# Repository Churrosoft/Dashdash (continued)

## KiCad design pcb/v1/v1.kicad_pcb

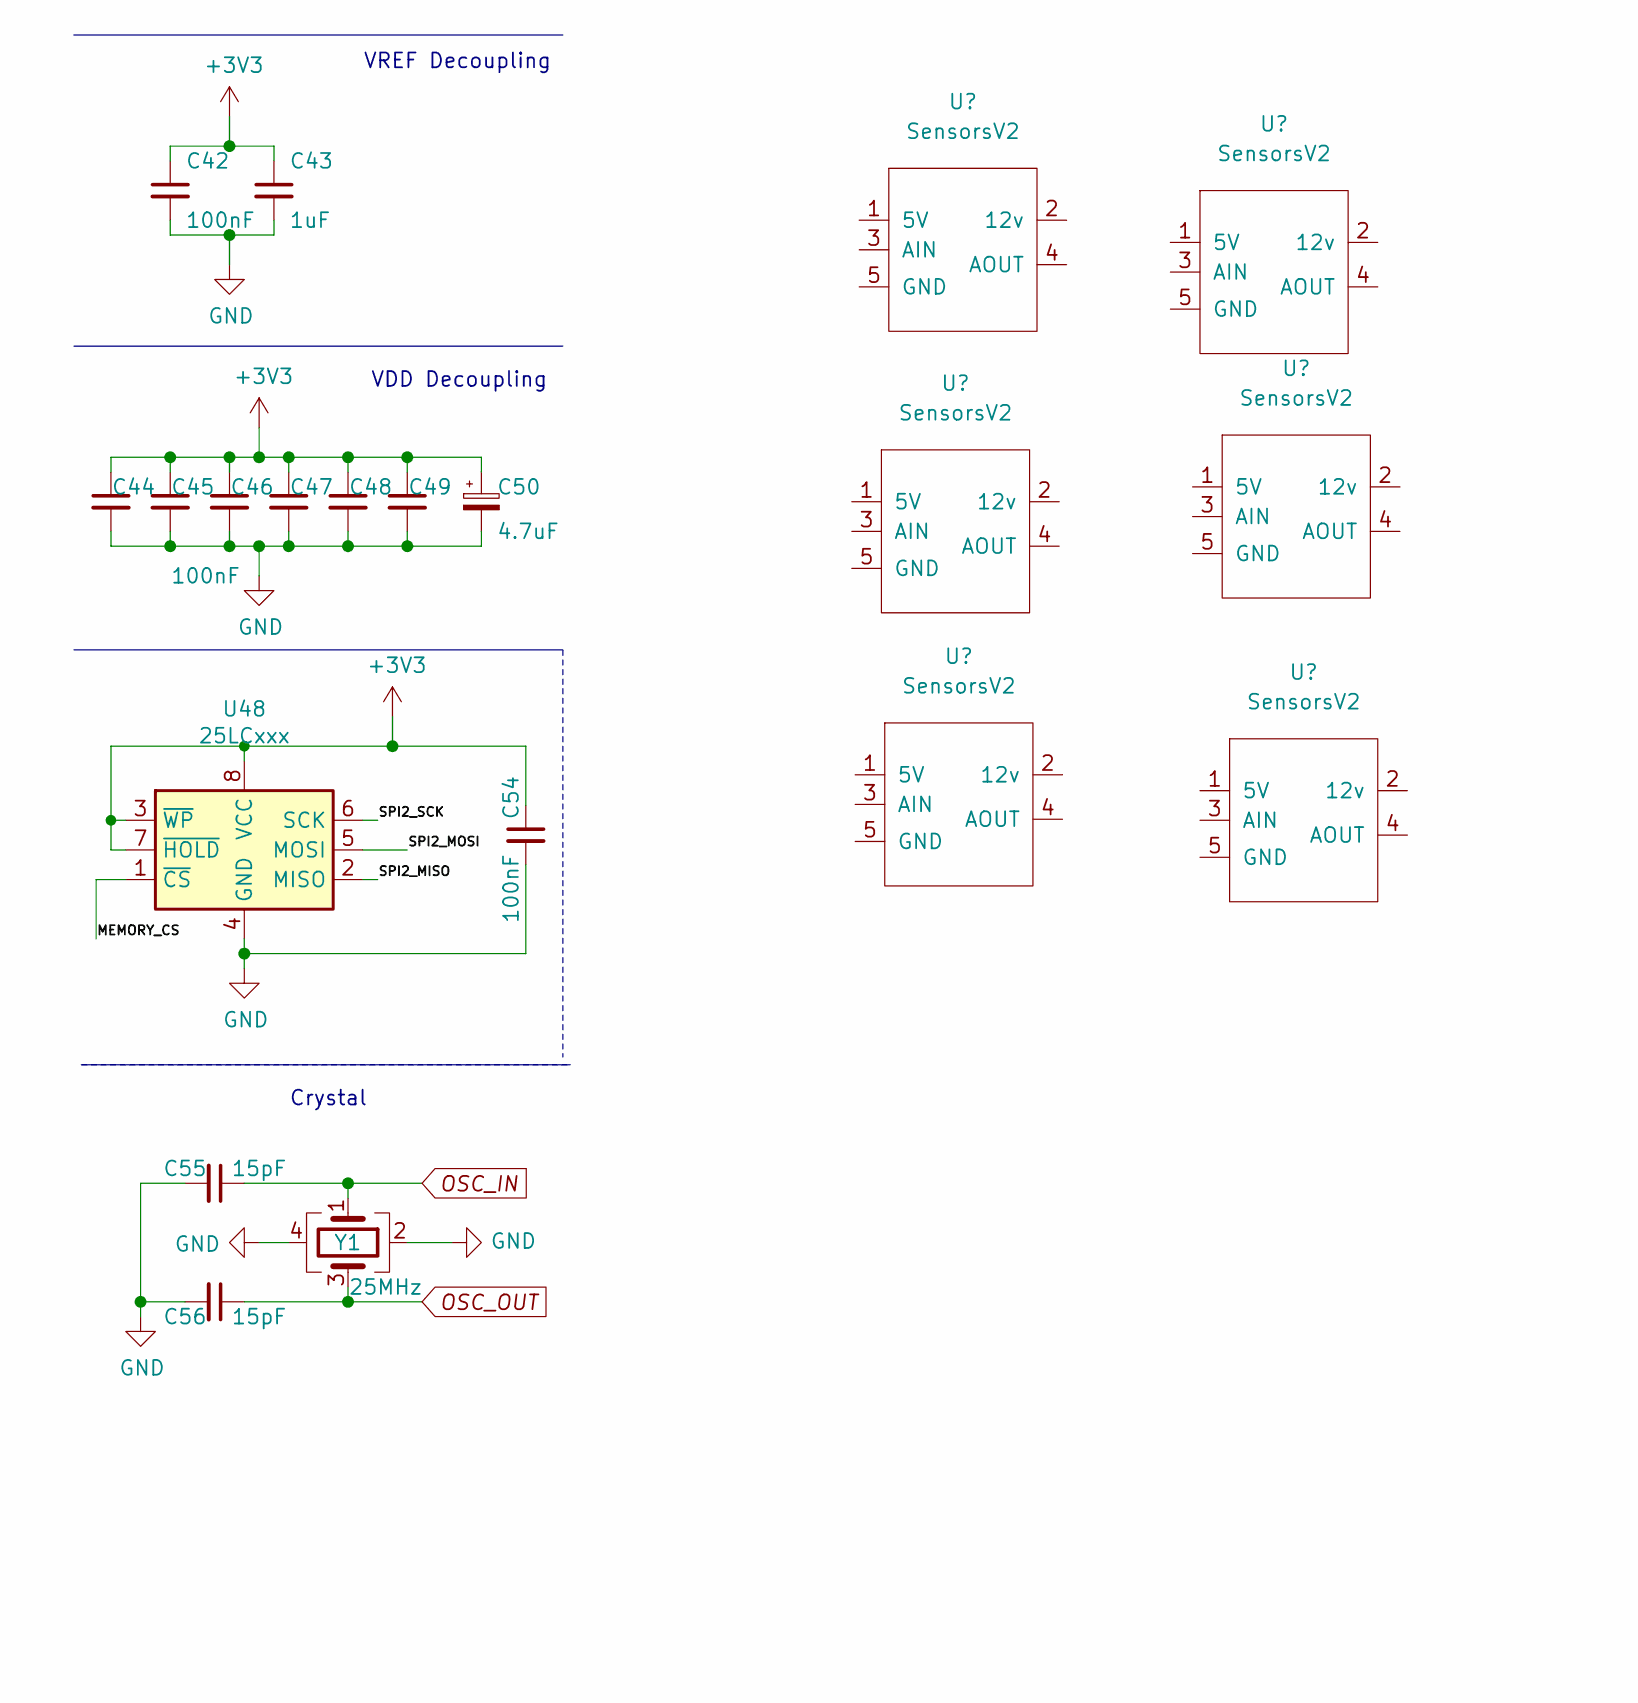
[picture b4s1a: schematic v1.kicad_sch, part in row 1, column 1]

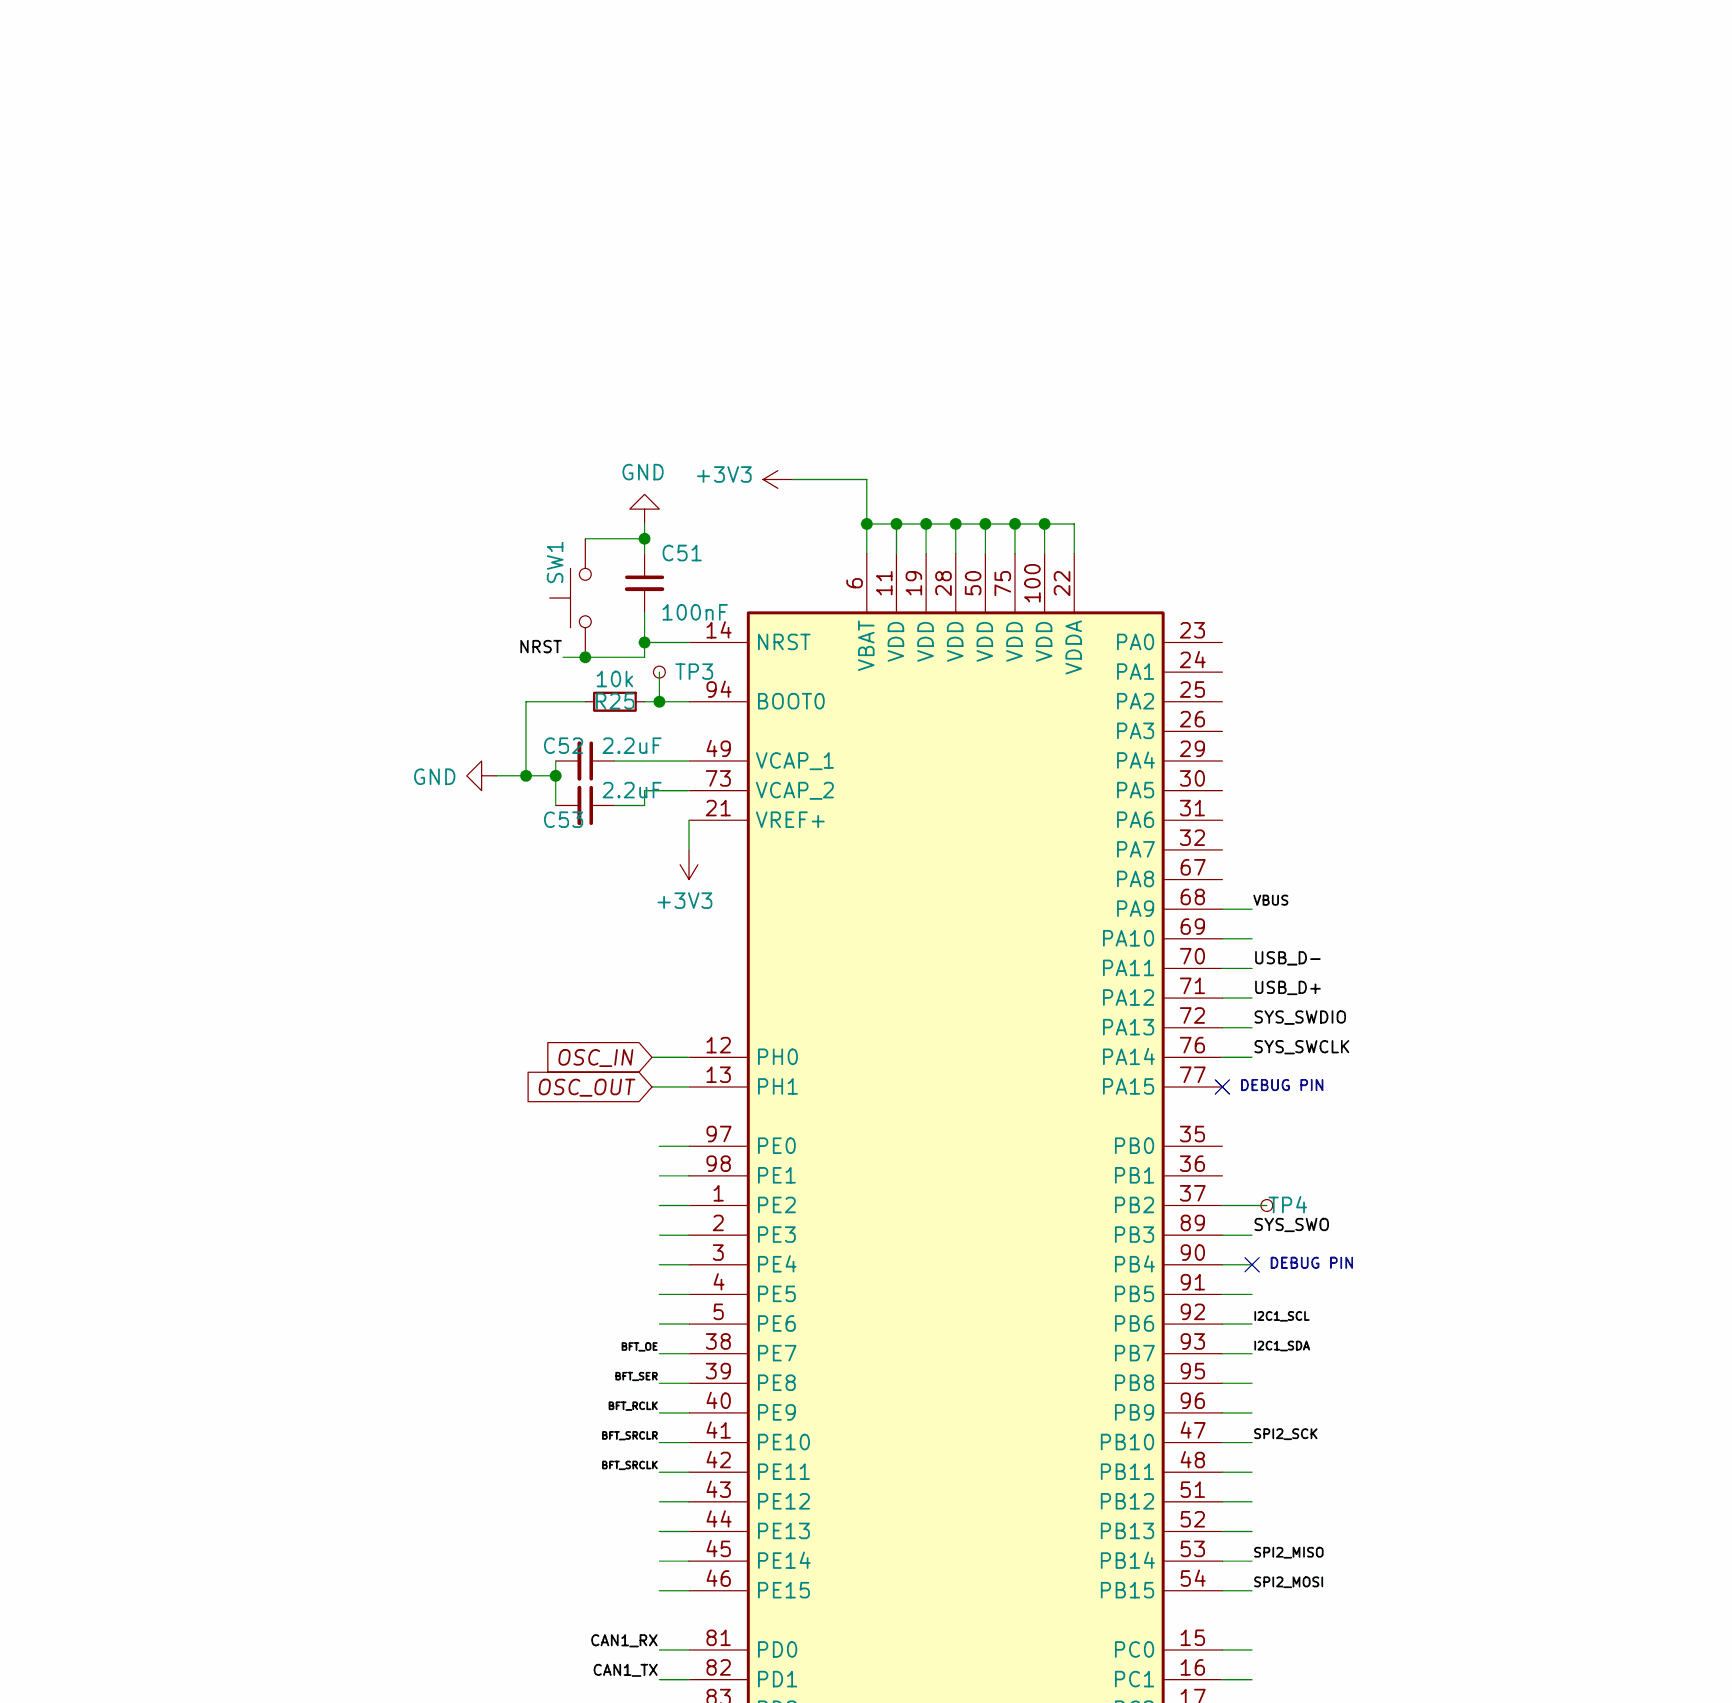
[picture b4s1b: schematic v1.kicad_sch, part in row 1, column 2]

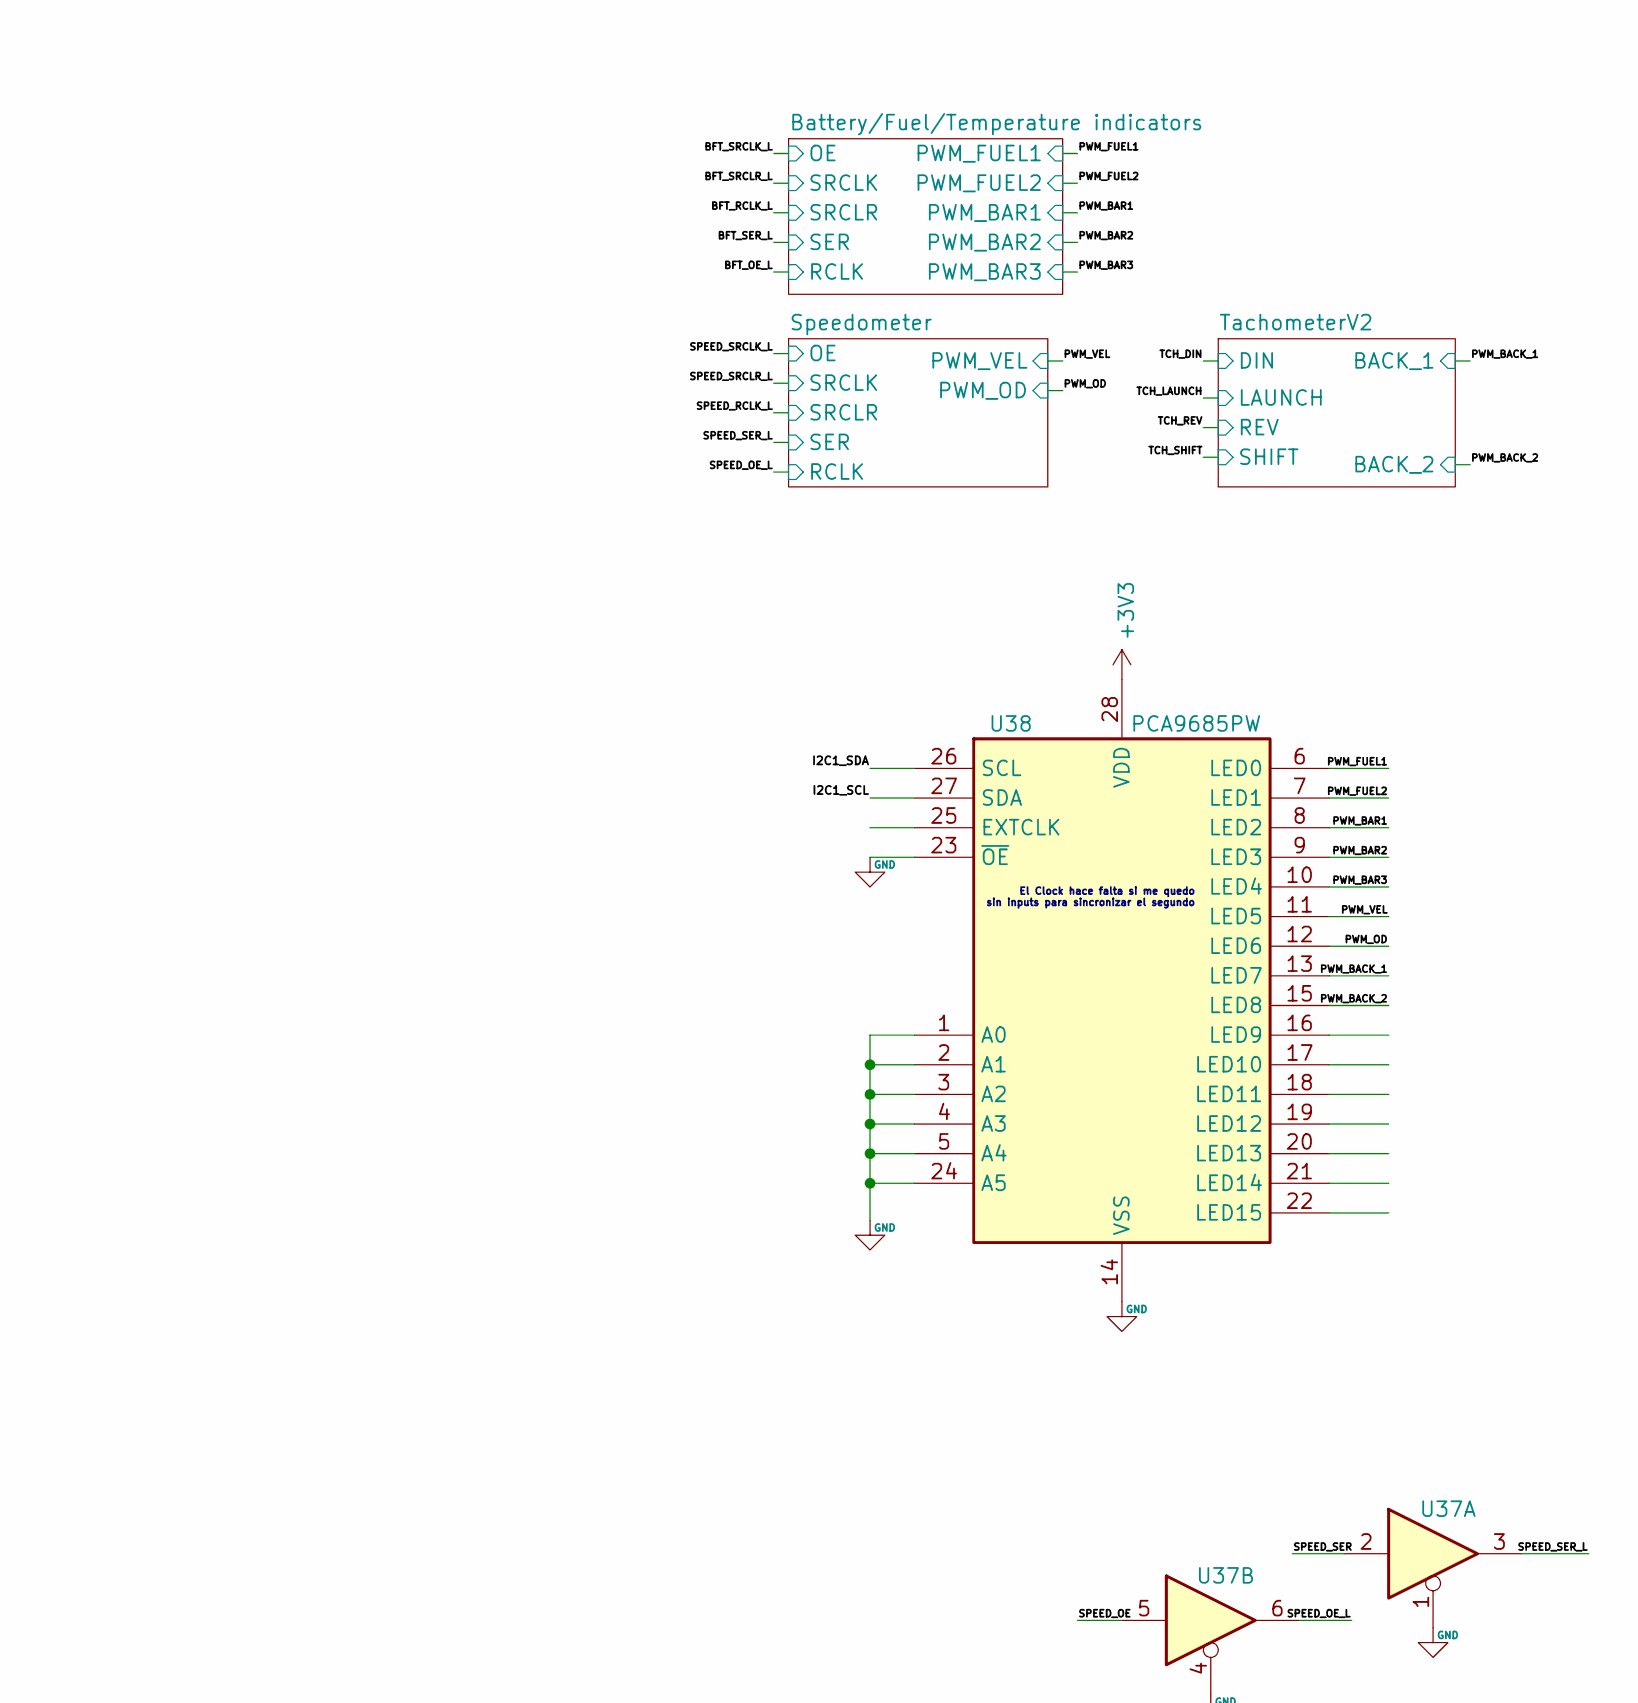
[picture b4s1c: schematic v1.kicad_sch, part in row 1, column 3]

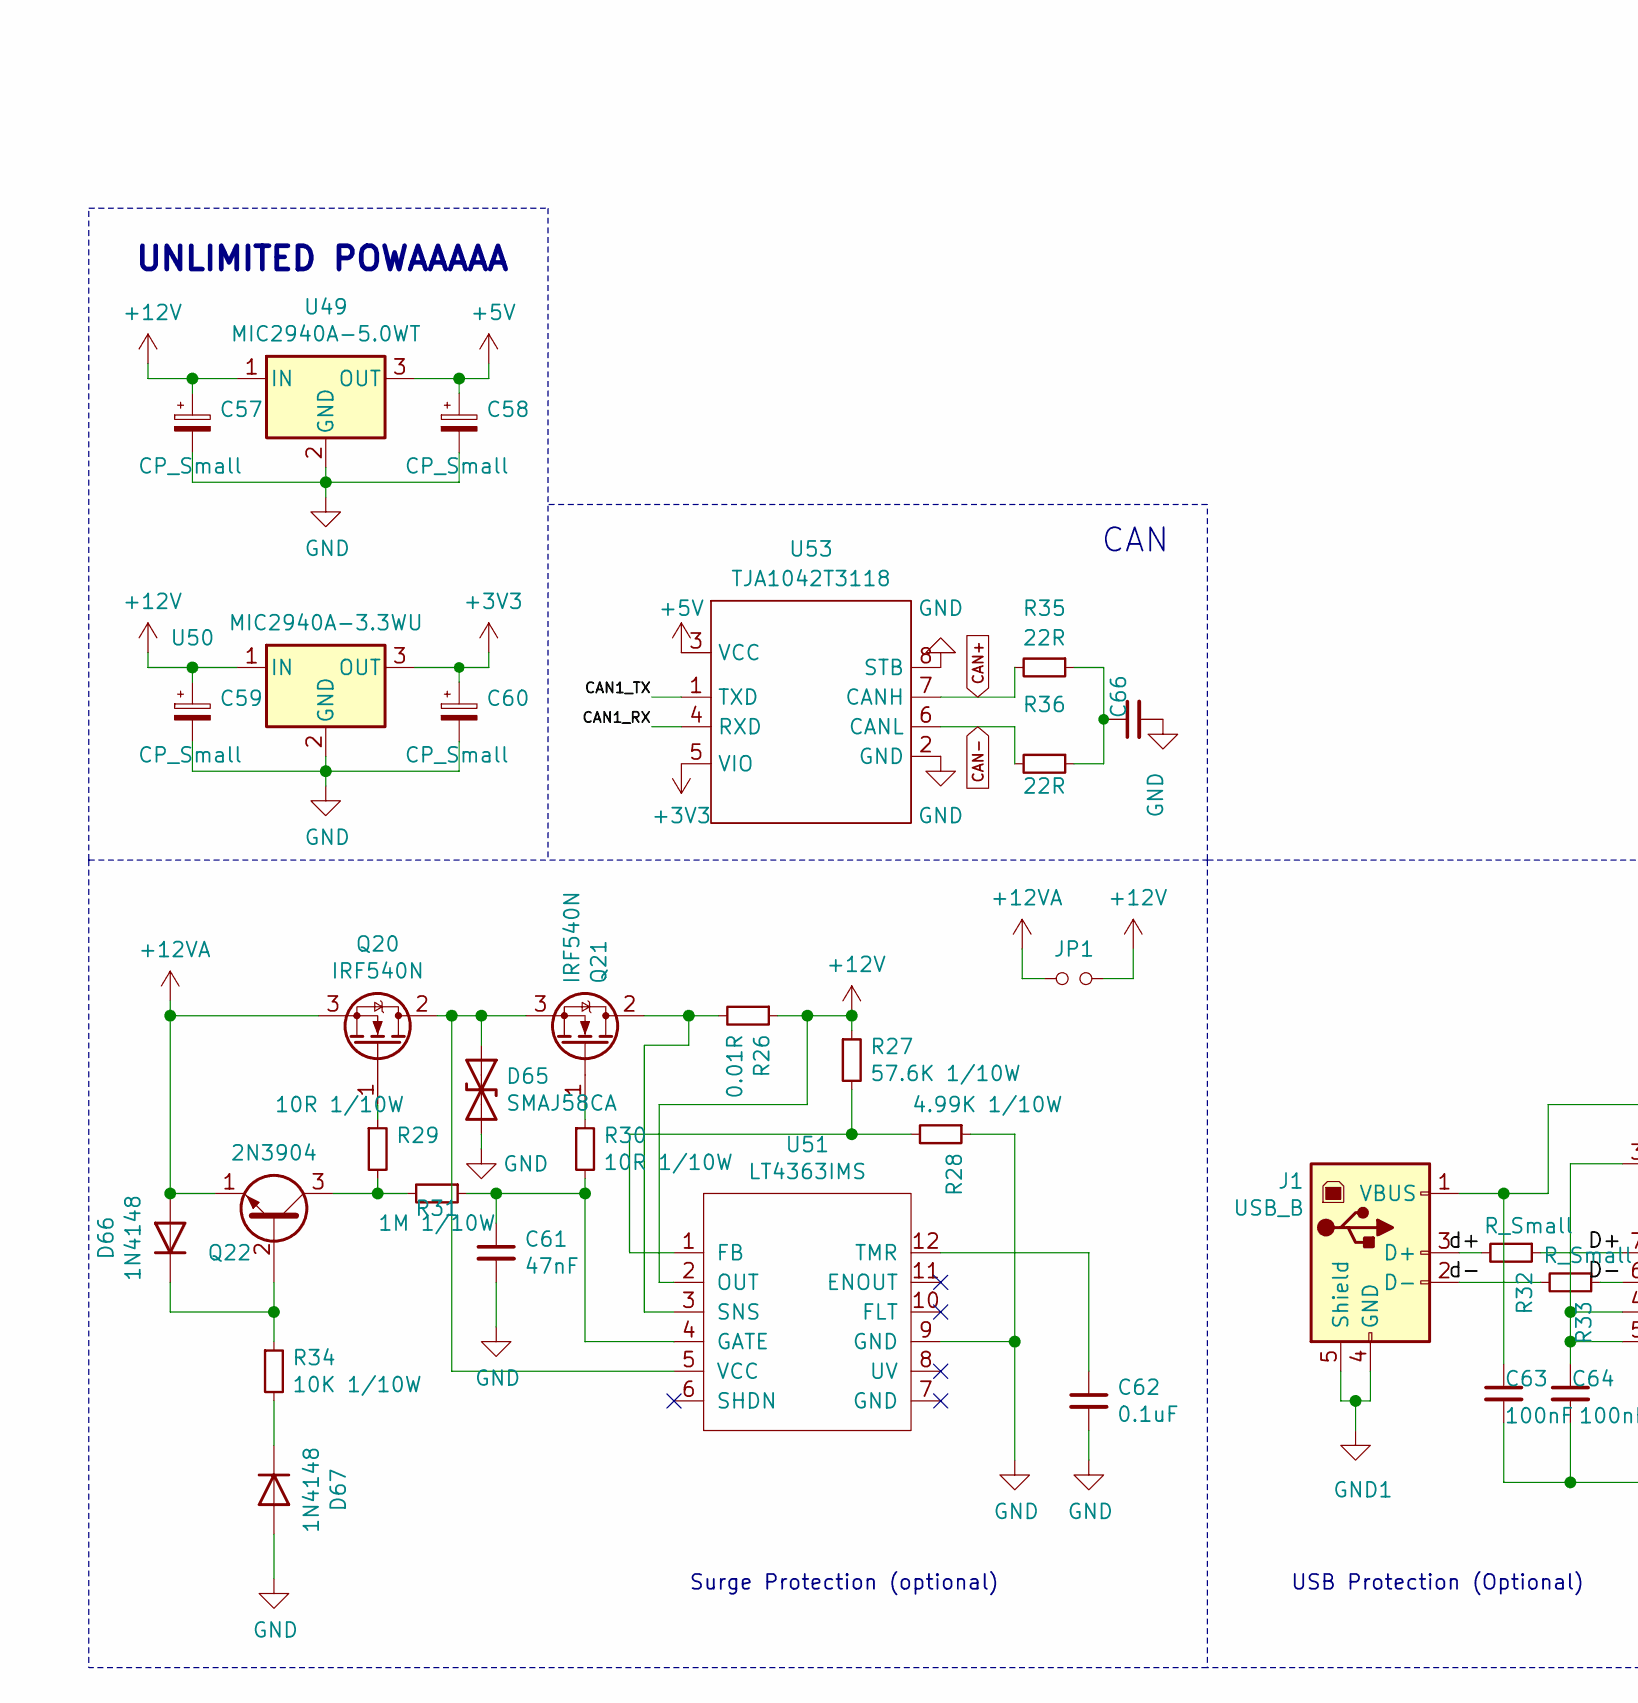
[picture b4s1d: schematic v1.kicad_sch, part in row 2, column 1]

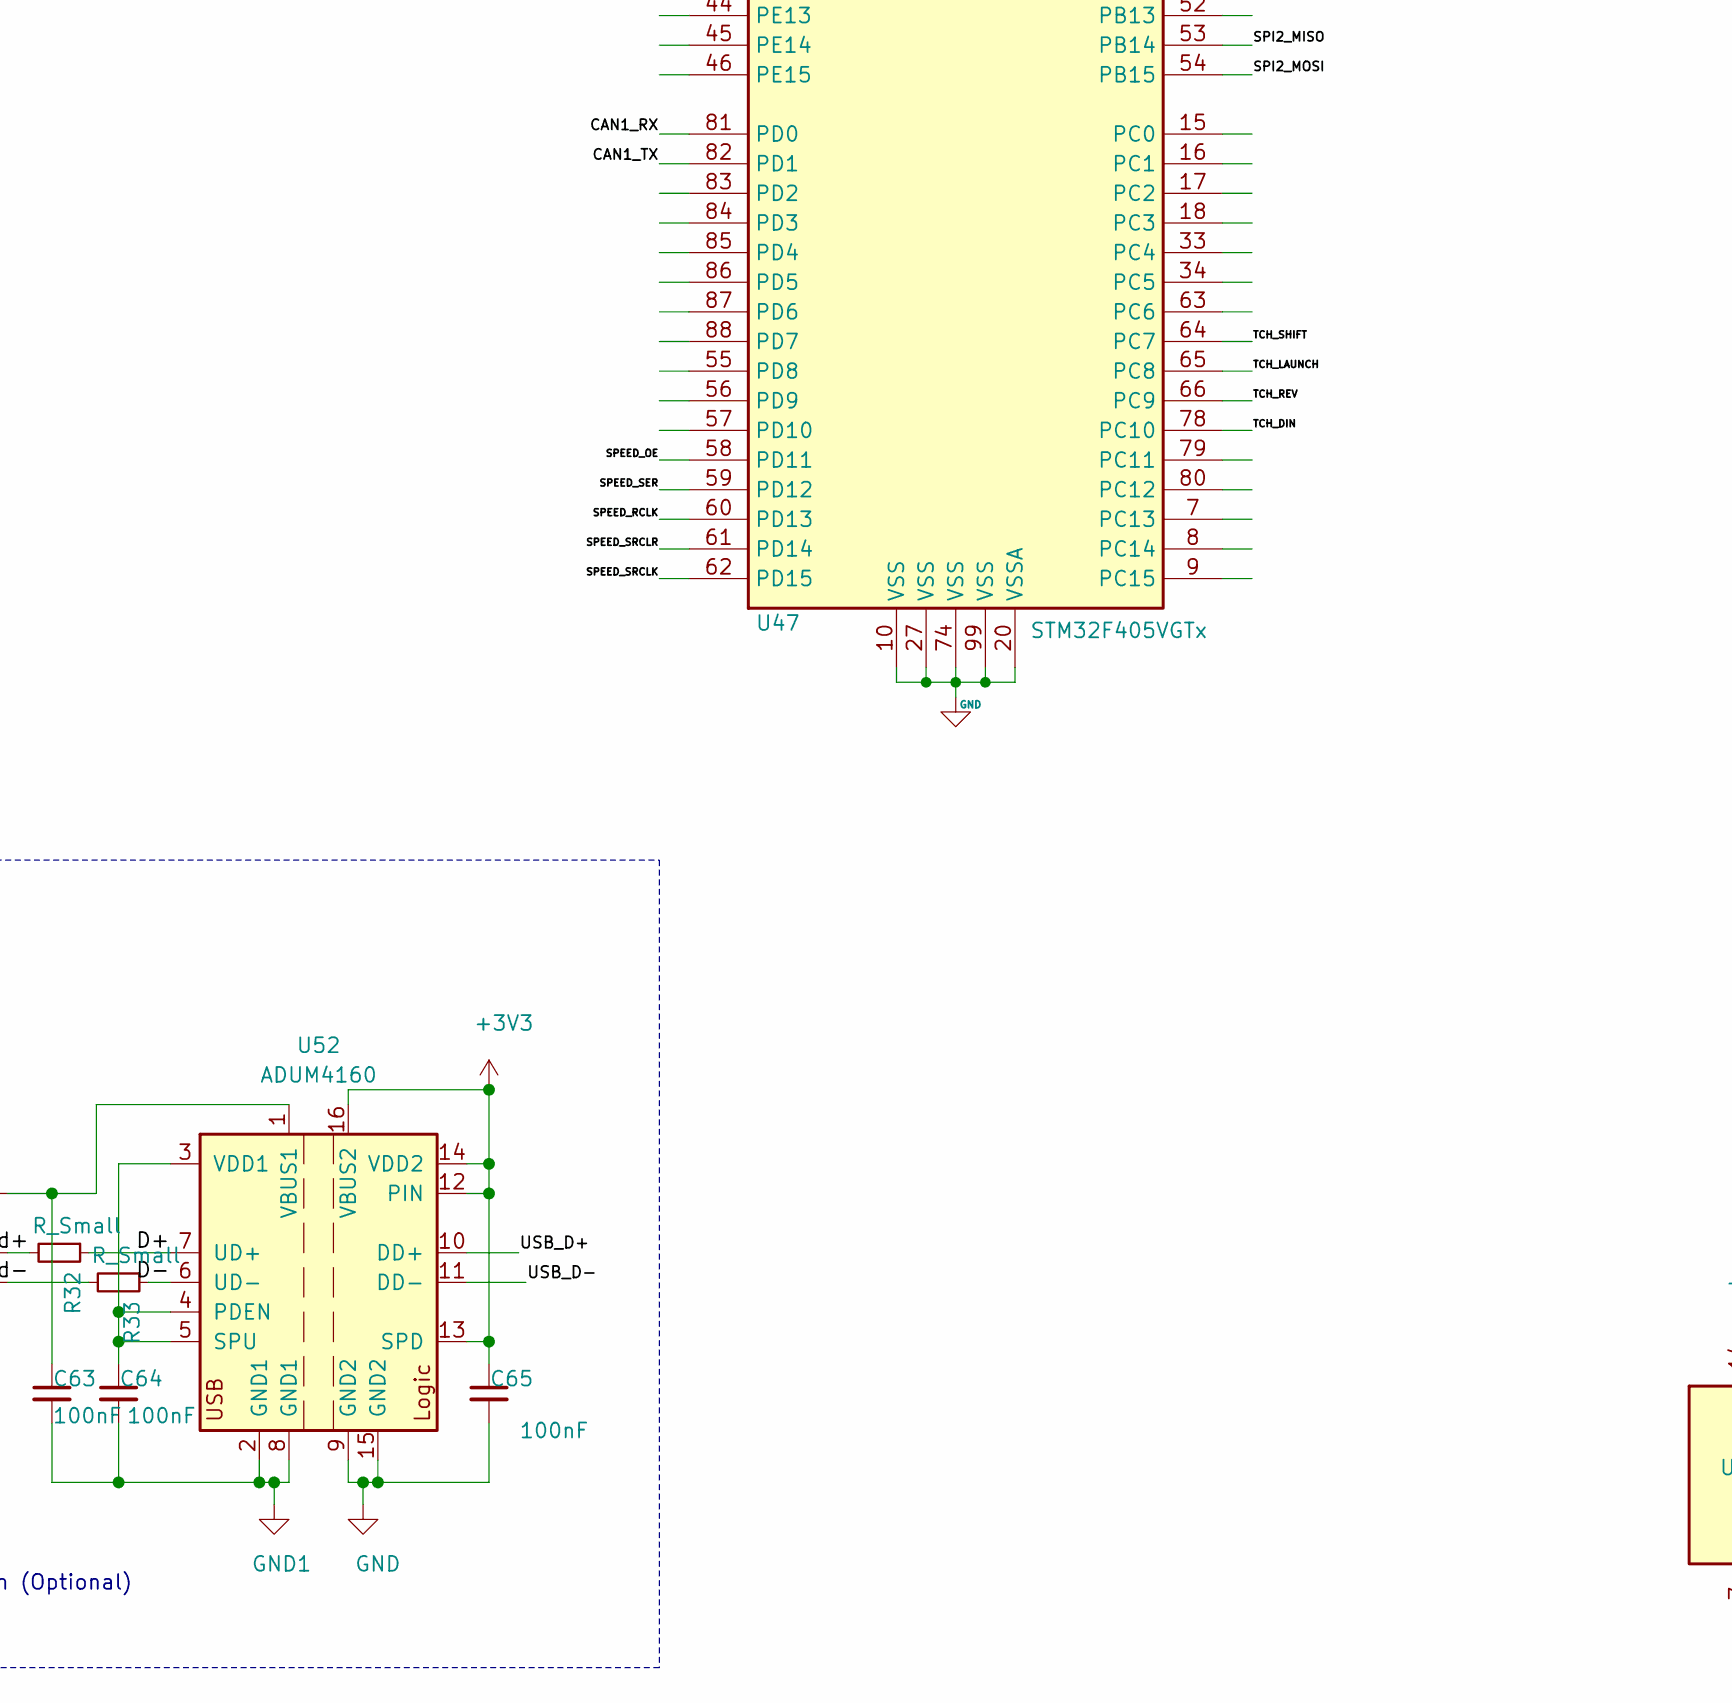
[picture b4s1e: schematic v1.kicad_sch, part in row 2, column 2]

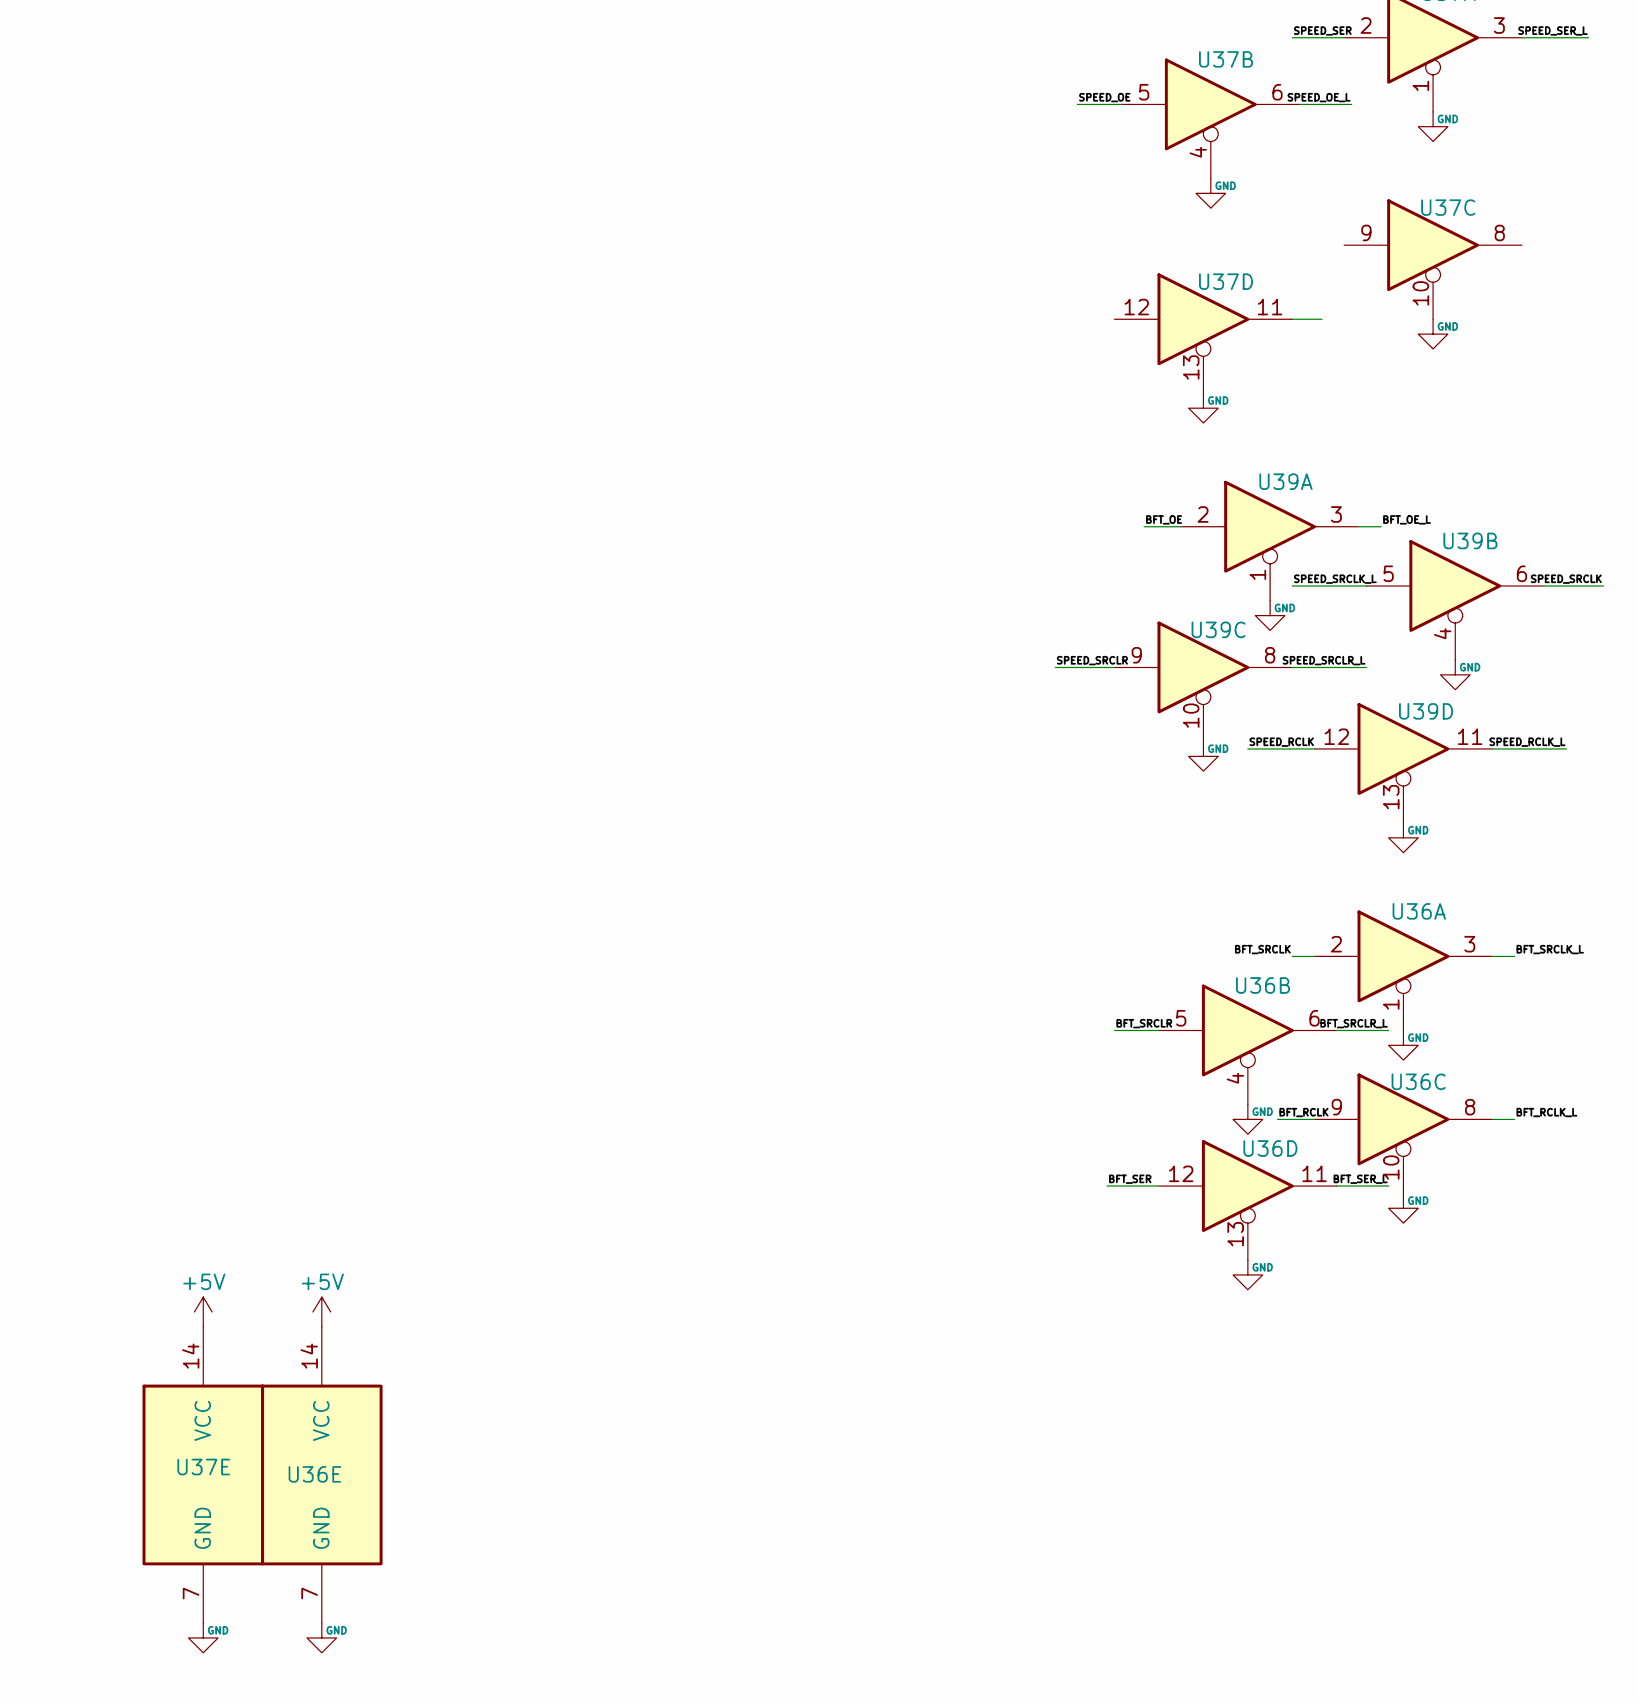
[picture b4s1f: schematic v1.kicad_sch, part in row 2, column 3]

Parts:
C42, C44, C45, C46, C47, C48, C49, C51, C54, C63, C64, C65: 100nF; C_0805_2012Metric; LCSC C49678
C43: 1uF; C_0805_2012Metric; LCSC C28323
C50: 4.7uF; C_0805_2012Metric; LCSC 0805
C52, C53: 2.2uF; C_0805_2012Metric; LCSC C49217
C55, C56: 15pF; C_0805_2012Metric; LCSC C1794
C57, C58, C59, C60: CP_Small
C61: 47nF; C_0603_1608Metric
C62: 0.1uF; C_0603_1608Metric
C66: 4.7nF; C_0805_2012Metric; LCSC C77475
D65: SMAJ58CA; D_SMA
D66, D67: 1N4148; D_0805_2012Metric
J1: USB_B; USB_B_OST_USB-B1HSxx_Horizontal
JP1: Jumper_NO_Small; SolderJumper-2_P1.3mm_Open_TrianglePad1.0x1.5mm
Q20, Q21: IRF540N; TO-220-3_Vertical
Q22: 2N3904; TSOT-23
R25: 10k; R_0603_1608Metric
R26: 0.01R; R_1210_3225Metric; LCSC C175884
R27: 57.6K 1/10W; R_0603_1608Metric
R28: 4.99K 1/10W; R_0603_1608Metric
R29, R30: 10R 1/10W; R_0603_1608Metric
R31: 1M 1/10W; R_0603_1608Metric
R32, R33: R_Small; R_0603_1608Metric
R34: 10K 1/10W; R_0603_1608Metric
R35, R36: 22R; R_1206_3216Metric; LCSC C205298
SW1: SW_Push; SW_SPST_TL3342
TP3: BOOT0; TestPoint_Pad_D2.0mm
TP4: BOOT1; TestPoint_Pad_D2.0mm
U36, U37, U39: 74LS125
U38: PCA9685PW; TSSOP-28_4.4x9.7mm_P0.65mm
U47: STM32F405VGTx; LQFP-100_14x14mm_P0.5mm
U48: 25LCxxx; SOIC-8_3.9x4.9mm_P1.27mm
U49: MIC2940A-5.0WT; TO-220-3_Vertical
U50: MIC2940A-3.3WU; TO-263-3_TabPin2
U51: LT4363IMS; SOIC-16W_7.5x10.3mm_P1.27mm
U52: ADUM4160; SOIC-16W_7.5x10.3mm_P1.27mm
U53: TJA1042T3118; HTSOP-8-1EP_3.9x4.9mm_P1.27mm_EP2.4x3.2mm
Y1: 25MHz; Crystal_SMD_3225-4Pin_3.2x2.5mm

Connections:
+3V3: C42.1, C43.1, C44.1, C45.1, C46.1, C47.1, C48.1, C49.1, C50.1, C54.1, C60.1, C65.1, U38.28 (VDD), U47.6 (VBAT), U47.11 (VDD), U47.19 (VDD), U47.21 (VREF+), U47.22 (VDDA), U47.28 (VDD), U47.50 (VDD), U47.75 (VDD), U47.100 (VDD), U48.3 (~WP), U48.7 (~HOLD), U48.8 (VCC), U50.3 (OUT), U52.12 (PIN), U52.13 (SPD), U52.14 (VDD2), U52.16 (VBUS2), U53.5 (VIO)
+12VA: D66.2 (A), JP1.1, Q20.3 (S), Q22.1 (E)
/BFT_OE: U39.2, U47.38 (PE7)
/BFT_RCLK: U36.9, U47.40 (PE9)
/BFT_SER: U36.12, U47.39 (PE8)
/BFT_SRCLK: U36.2, U47.42 (PE11)
/BFT_SRCLR: U36.5, U47.41 (PE10)
/CAN1_RX: U47.81 (PD0), U53.4 (RXD)
/CAN1_TX: U47.82 (PD1), U53.1 (TXD)
/D+: R32.1, U52.7 (UD+)
/D-: R33.1, U52.6 (UD-)
/I2C1_SCL: U38.27 (SDA), U47.92 (PB6)
/I2C1_SDA: U38.26 (SCL), U47.93 (PB7)
/MEMORY_CS: U48.1 (~CS)
/NRST: C51.2, SW1.1, U47.14 (NRST)
/PWM_BACK_1: U38.13 (LED7); also elsewhere on the board
/PWM_BACK_2: U38.15 (LED8); also elsewhere on the board
/PWM_BAR1: U38.8 (LED2); also elsewhere on the board
/PWM_BAR2: U38.9 (LED3); also elsewhere on the board
/PWM_BAR3: U38.10 (LED4); also elsewhere on the board
/PWM_FUEL1: U38.6 (LED0); also elsewhere on the board
/PWM_FUEL2: U38.7 (LED1)
/PWM_OD: U38.12 (LED6); also elsewhere on the board
/PWM_VEL: U38.11 (LED5); also elsewhere on the board
/SPEED_OE: U37.5, U47.58 (PD11)
/SPEED_RCLK: U39.12, U47.60 (PD13)
/SPEED_SER: U37.2, U47.59 (PD12)
/SPEED_SRCLK: U39.6, U47.62 (PD15)
/SPEED_SRCLR: U39.9, U47.61 (PD14)
/SPI2_MISO: U47.53 (PB14), U48.2 (MISO)
/SPI2_MOSI: U47.54 (PB15), U48.5 (MOSI)
/SPI2_SCK: U47.47 (PB10), U48.6 (SCK)
/SYS_SWCLK: U47.76 (PA14)
/SYS_SWDIO: U47.72 (PA13)
/SYS_SWO: U47.89 (PB3)
/TCH_DIN: U47.78 (PC10); also elsewhere on the board
/TCH_LAUNCH: U47.65 (PC8); also elsewhere on the board
/TCH_REV: U47.66 (PC9); also elsewhere on the board
/TCH_SHIFT: U47.64 (PC7); also elsewhere on the board
/USB_D+: U47.71 (PA12), U52.10 (DD+)
/USB_D-: U47.70 (PA11), U52.11 (DD-)
/VBUS: U47.68 (PA9)
/d+: J1.3 (D+), R32.2
/d-: J1.2 (D-), R33.2
CAN+: R35.2, U53.7 (CANH)
CAN-: R36.2, U53.6 (CANL)
GND: C42.2, C43.2, C44.2, C45.2, C46.2, C47.2, C48.2, C49.2, C50.2, C51.1, C52.2, C53.2, C54.2, C55.2, C56.2, C57.2, C58.2, C59.2, C60.2, C61.2, C62.2, C65.2, C66.2, D65.2 (A2), D67.2 (A), R25.2, R28.1, SW1.2, U36.1, U36.4, U36.7 (GND), U36.10, U36.13, U37.1, U37.4, U37.7 (GND), U37.10, U37.13, U38.1 (A0), U38.2 (A1), U38.3 (A2), U38.4 (A3), U38.5 (A4), U38.14 (VSS), U38.23 (~OE), U38.24 (A5), U39.1, U39.4, U39.10, U39.13, U47.10 (VSS), U47.20 (VSSA), U47.27 (VSS), U47.74 (VSS), U47.99 (VSS), U48.4 (GND), U49.2 (GND), U50.2 (GND), U51.9 (GND), U52.9 (GND2), U52.15 (GND2), U53.2 (GND), U53.8 (STB), Y1.2, Y1.4; also elsewhere on the board
GND1: C63.2, C64.2, J1.4 (GND), J1.5 (Shield), U52.2 (GND1), U52.8 (GND1)
unnamed: C52.1, U47.49 (VCAP_1)
unnamed: C53.1, U47.73 (VCAP_2)
unnamed: C61.1, R30.2, R31.1, U51.4 (GATE)
unnamed: C62.1, U51.12 (TMR)
unnamed: C63.1, J1.1 (VBUS), U52.1 (VBUS1)
unnamed: C64.1, U52.3 (VDD1), U52.4 (PDEN), U52.5 (SPU)
unnamed: C66.1, R35.1, R36.1
unnamed: D65.1 (A1), Q20.2 (D), Q21.3 (S), U51.5 (VCC)
unnamed: D66.1 (K), Q22.2 (B), R34.1
unnamed: D67.1 (K), R34.2
unnamed: Q20.1 (G), R29.1
unnamed: Q21.1 (G), R30.1
unnamed: Q21.2 (D), R26.2, U51.3 (SNS)
unnamed: Q22.3 (C), R29.2, R31.2
unnamed: R25.1, TP3.1, U47.94 (BOOT0)
unnamed: R27.2, R28.2, U51.1 (FB)
unnamed: TP4.1, U47.37 (PB2)
OSC_IN: C55.1, U47.12 (PH0), Y1.1
OSC_OUT: C56.1, U47.13 (PH1), Y1.3

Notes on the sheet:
Crystal
VREF Decoupling
VDD Decoupling
UNLIMITED POWAAAAA
Surge Protection (optional)
CAN
USB Protection (Optional)
DEBUG PIN
El Clock hace falta si me quedo sin inputs para sincronizar el segundo
